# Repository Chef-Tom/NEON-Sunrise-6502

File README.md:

# NEON-Sunrise-6502
The 6502 based Prototypes

This started in early 2021 as a work from hom distraction and quickly grew into an obsession.
This repository is to work in conjuction with the blog at http://realcheftom.com/6502
and my YouTube documentation of the project at https://www.youtube.com/watch?v=W5MUhNn74IM&list=PLEm9BpY3woKBx9LlBmEiw2NBphkDs04n8

Comments and updates welcome!

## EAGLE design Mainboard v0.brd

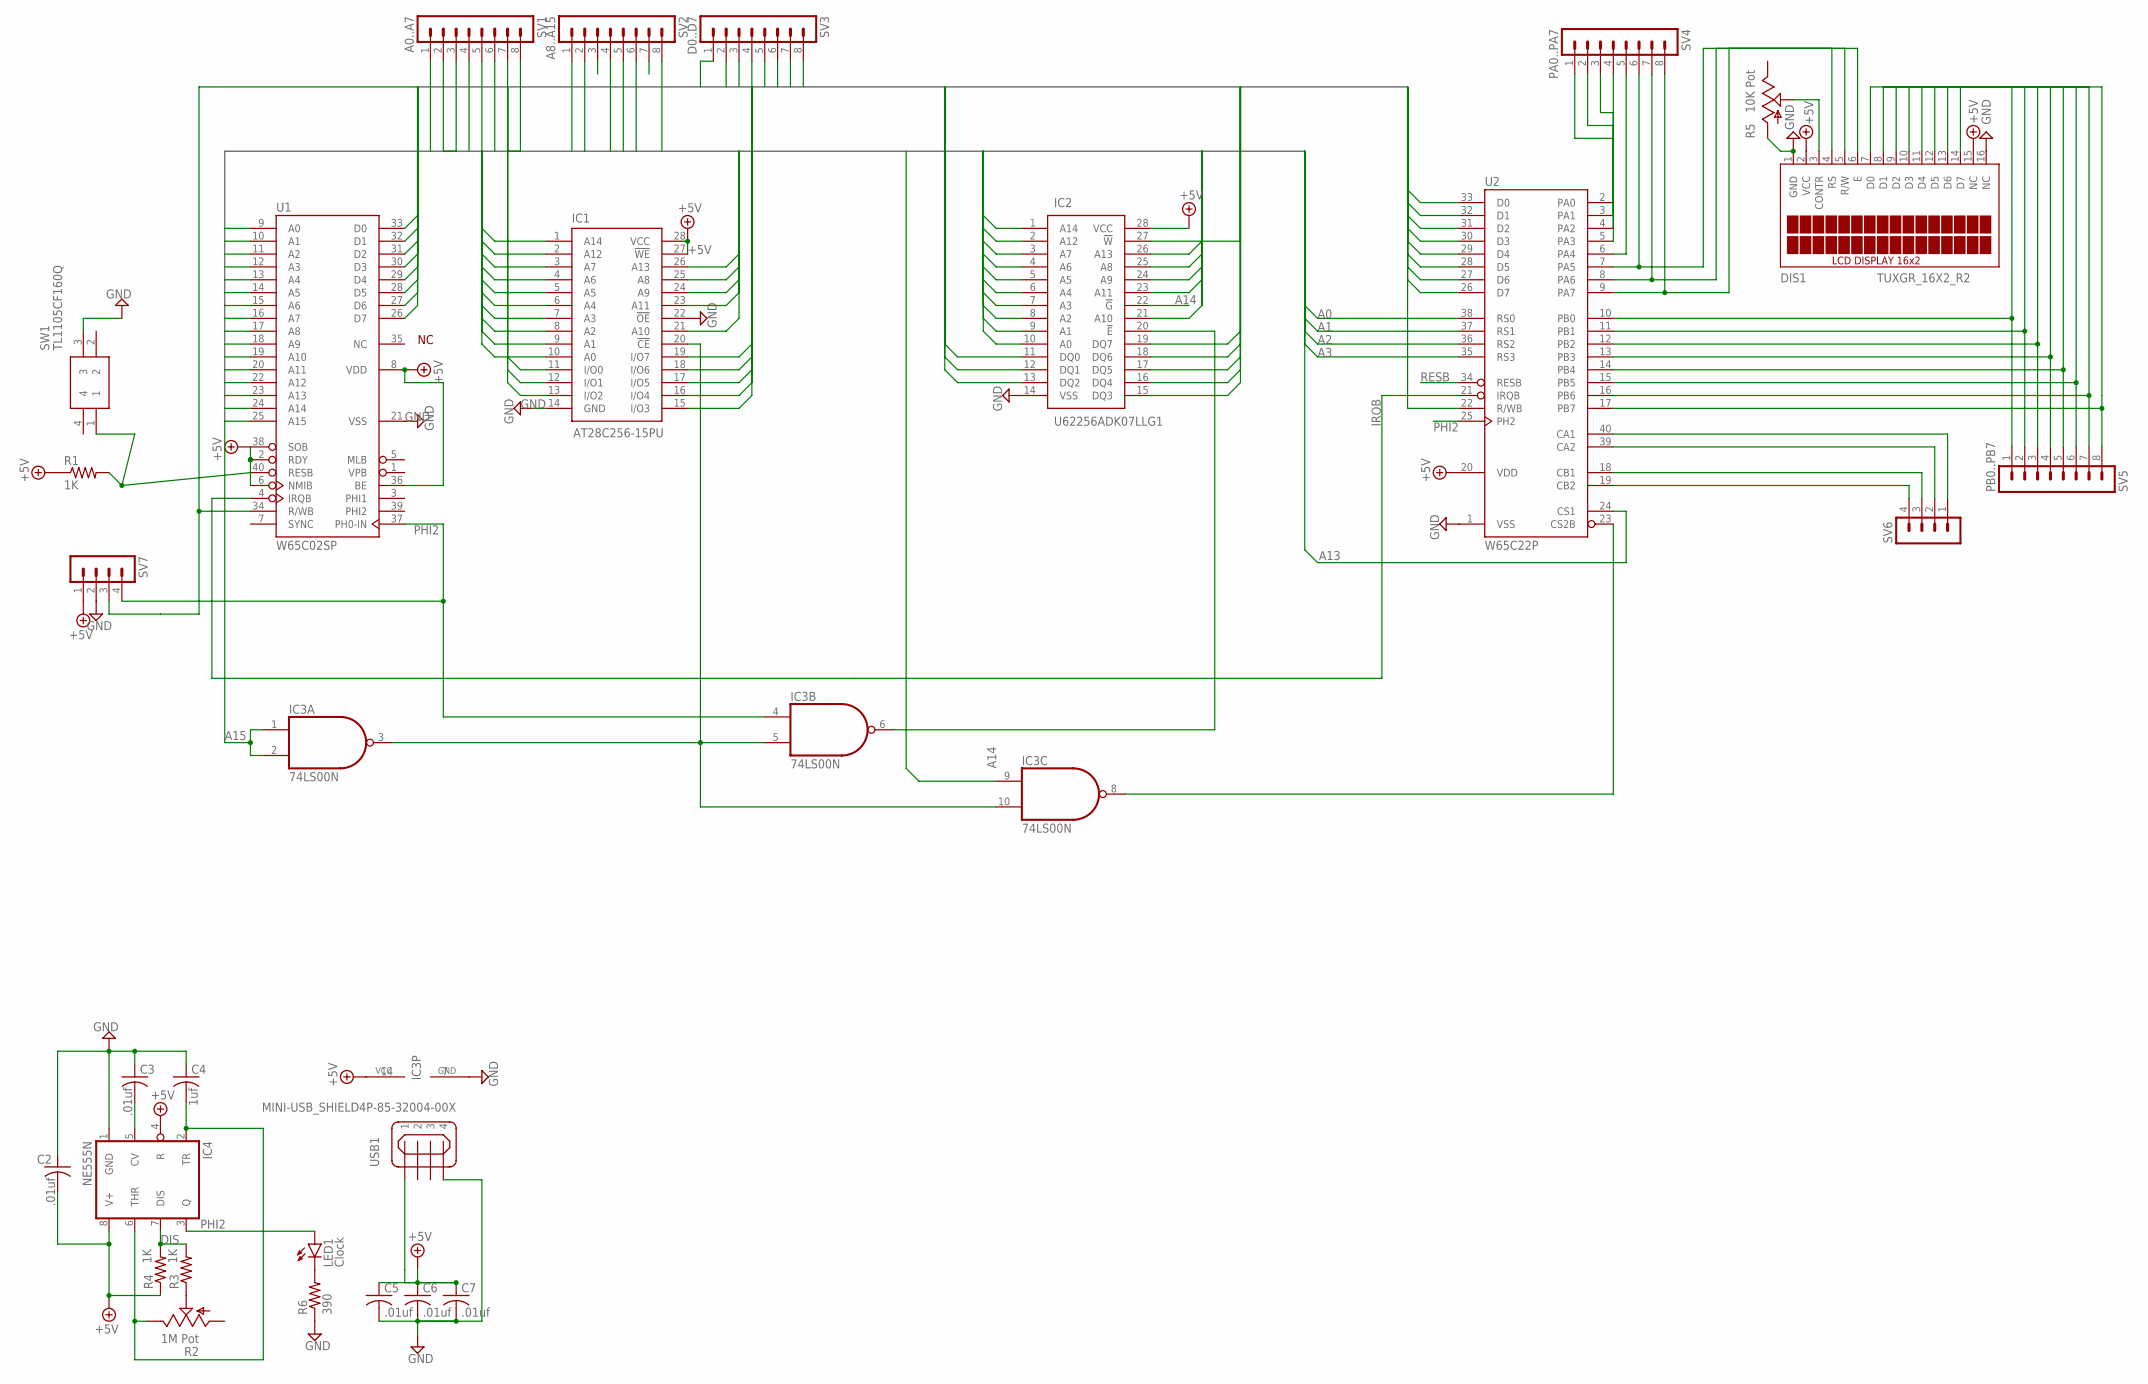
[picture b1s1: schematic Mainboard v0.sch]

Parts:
C2, C3, C5, C6, C7: .01uf; C075-032X103
C4: 1uf; C075-032X103
DIS1: TUXGR_16X2_R2
IC1: AT28C256-15PU; DIP1556W56P254L3702H483Q28N
IC2: U62256ADK07LLG1; DIP1524W59P254L3710H510Q28N
IC3: 74LS00N; DIL14
IC4: NE555N; DIL08
LED1: Clock; LED5MM
R1, R3, R4: 1K; 0204/7
R2: 1M Pot; B25U
R5: 10K Pot; B25U
R6: 390; 0204/7
SV1: A0..A7; MA08-1
SV2: A8..A15; MA08-1
SV3: D0..D7; MA08-1
SV4: PA0..PA7; MA08-1
SV5: PB0..PB7; MA08-1
SV6, SV7: MA04-1
SW1: TL1105CF160Q
U1: W65C02SP; DIP-40
U2: W65C22P; DIP-40
USB1: MINI-USB_SHIELD4P-85-32004-00X; 85-32004-00X

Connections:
+5V: C2.2, C5.1, C6.1, C7.1, DIS1.2 (VCC), DIS1.15 (NC), IC1.27 (!WE), IC1.28 (VCC), IC2.28 (VCC), IC3.14 (VCC), IC4.4 (R), IC4.8 (V+), R1.1, R4.1, SV7.1, U1.2 (RDY), U1.6 (NMIB), U1.8 (VDD), U1.36 (BE), U1.38 (SOB), U2.20 (VDD), USB1.1
A0: IC1.10 (A0), IC2.10 (A0), SV1.1, U1.9 (A0), U2.38 (RS0)
A1: IC1.9 (A1), IC2.9 (A1), SV1.2, U1.10 (A1), U2.37 (RS1)
A2: IC1.8 (A2), IC2.8 (A2), SV1.3, U1.11 (A2), U2.36 (RS2)
A3: IC1.7 (A3), IC2.7 (A3), SV1.4, U1.12 (A3), U2.35 (RS3)
A4: IC1.6 (A4), IC2.6 (A4), SV1.5, U1.13 (A4)
A5: IC1.5 (A5), IC2.5 (A5), SV1.6, U1.14 (A5)
A6: IC1.4 (A6), IC2.4 (A6), SV1.7, U1.15 (A6)
A7: IC1.3 (A7), IC2.3 (A7), SV1.8, U1.16 (A7)
A8: IC1.25 (A8), IC2.25 (A8), SV2.1, U1.17 (A8)
A9: IC1.24 (A9), IC2.24 (A9), SV2.2, U1.18 (A9)
A10: IC1.21 (A10), IC2.21 (A10), SV2.3, U1.19 (A10)
A11: IC1.23 (A11), IC2.23 (A11), SV2.4, U1.20 (A11)
A12: IC1.2 (A12), IC2.2 (A12), SV2.5, U1.22 (A12)
A13: IC1.26 (A13), IC2.26 (A13), SV2.6, U1.23 (A13), U2.24 (CS1)
A14: IC1.1 (A14), IC2.1 (A14), IC2.22 (!G), IC3.9 (I0), SV2.7, U1.24 (A14)
A15: IC3.1 (I0), IC3.2 (I1), SV2.8, U1.25 (A15)
CLK-1: C4.2, IC4.2 (TR), IC4.6 (THR), R2.E
D0: IC1.11 (I/O0), IC2.11 (DQ0), SV3.1, U1.33 (D0), U2.33 (D0)
D1: IC1.12 (I/O1), IC2.12 (DQ1), SV3.2, U1.32 (D1), U2.32 (D1)
D2: IC1.13 (I/O2), IC2.13 (DQ2), SV3.3, U1.31 (D2), U2.31 (D2)
D3: IC1.15 (I/O3), IC2.15 (DQ3), SV3.4, U1.30 (D3), U2.30 (D3)
D4: IC1.16 (I/O4), IC2.16 (DQ4), U1.29 (D4), U2.29 (D4)
D5: IC1.17 (I/O5), IC2.17 (DQ5), SV3.5, SV3.6, U1.28 (D5), U2.28 (D5)
D6: IC1.18 (I/O6), IC2.18 (DQ6), SV3.7, U1.27 (D6), U2.27 (D6)
D7: IC1.19 (I/O7), IC2.19 (DQ7), SV3.8, U1.26 (D7), U2.26 (D7)
DIS: IC4.7 (DIS), R3.2, R4.2
GND: C2.1, C3.1, C4.1, C5.2, C6.2, C7.2, DIS1.1 (GND), DIS1.16 (NC), IC1.14 (GND), IC1.22 (!OE), IC2.14 (VSS), IC3.7 (GND), IC4.1 (GND), R5.A, R6.1, SV7.2, SW1.3, U1.21 (VSS), U2.1 (VSS), USB1.4
IRQB: U1.4 (IRQB), U2.21 (IRQB)
unnamed: IC1.20 (!CE), IC3.3 (O), IC3.5 (I1), IC3.10 (I1)
unnamed: IC3.8 (O), U2.23 (CS2B)
unnamed: R2.S, R3.1
unnamed: C3.2, IC4.5 (CV)
unnamed: LED1.K (C), R6.2
unnamed: IC2.20 (!E), IC3.6 (O)
unnamed: DIS1.3 (CONTR), R5.S
unnamed: DIS1.7 (D0), SV5.1, U2.10 (PB0)
unnamed: DIS1.8 (D1), SV5.2, U2.11 (PB1)
unnamed: DIS1.9 (D2), SV5.3, U2.12 (PB2)
unnamed: DIS1.10 (D3), SV5.4, U2.13 (PB3)
unnamed: DIS1.11 (D4), SV5.5, U2.14 (PB4)
unnamed: DIS1.12 (D5), SV5.6, U2.15 (PB5)
unnamed: DIS1.13 (D6), SV5.7, U2.16 (PB6)
unnamed: DIS1.14 (D7), SV5.8, U2.17 (PB7)
unnamed: DIS1.6 (E), SV4.8, U2.9 (PA7)
unnamed: DIS1.5 (R/W), SV4.7, U2.8 (PA6)
unnamed: DIS1.4 (RS), SV4.6, U2.7 (PA5)
unnamed: SV4.1, U2.2 (PA0)
unnamed: SV4.2, U2.3 (PA1)
unnamed: SV4.3, U2.4 (PA2)
unnamed: SV4.4, U2.5 (PA3)
unnamed: SV4.5, U2.6 (PA4)
unnamed: SV6.1, U2.40 (CA1)
unnamed: SV6.2, U2.39 (CA2)
unnamed: SV6.3, U2.18 (CB1)
unnamed: SV6.4, U2.19 (CB2)
PHI2: IC3.4 (I0), IC4.3 (Q), LED1.A, SV7.4, U1.37 (PH0-IN), U2.25 (PH2)
RESB: R1.2, SW1.1, U1.40 (RESB), U2.34 (RESB)
RWB: IC2.27 (!W), SV7.3, U1.34 (R/WB), U2.22 (R/WB)

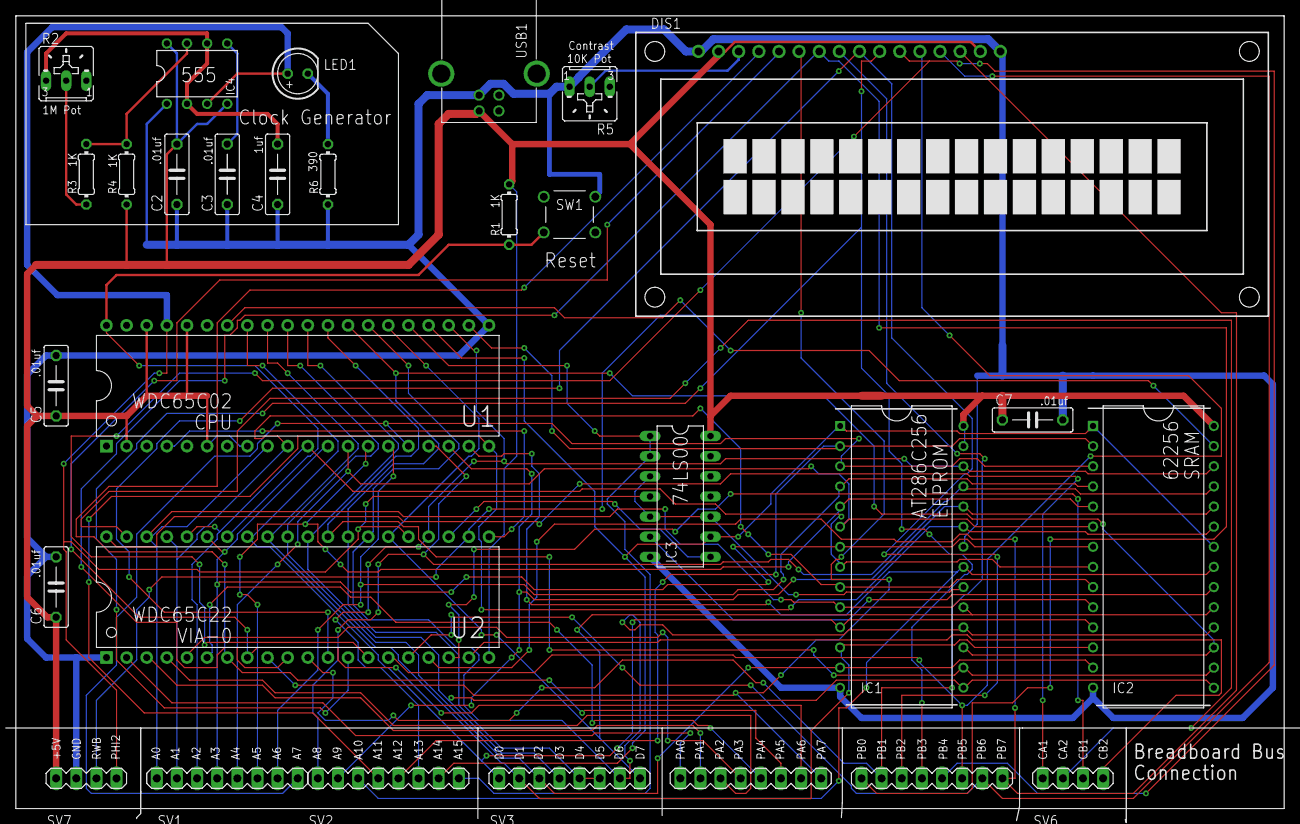
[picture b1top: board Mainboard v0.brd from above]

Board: 2 copper layers, 160.0 x 100.0 mm, 29 parts (0 on the bottom side), 59 nets.

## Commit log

2021-09-26 Add files via upload
    Initial upload using the V0.2 mainboard files and the four button interrupt test.
2022-01-17 Add files via upload
    After fixing the bus contention that arose from the ACIA addresses being a subset of the VIA addresses and not disabling the VIA, So that was fun.
